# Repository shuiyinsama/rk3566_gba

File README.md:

# rk3566_gba

RK3566 / Radxa CM3 掌机验证项目。当前第一验证目标是 GBA，第一阶段使用 Radxa CM3 IO Board + 4.3 寸 HDMI 屏完成系统、显示、输入、音频、散热和 GBA 模拟器验证；成品阶段再围绕目标 DSI 屏设计自研 CM3 底板。

## 构建

项目使用 CMake 管理。

Windows 开发机建议通过 WSL Ubuntu 构建，不需要 SSH 到 WSL。SSH 主要用于后续连接 Radxa CM3 板端做实际硬件验证。

```bash
cmake --preset debug
cmake --build --preset debug
ctest --preset debug
./build/debug/rk3566-gba --help
```

若之前在 Windows 原生路径下生成过 `build/debug`，切到 WSL 后可能遇到 CMake cache 路径不匹配。删除 `build/debug` 后重新运行 `cmake --preset debug` 即可。

## 开发助手

Windows 上可以启动 Python 图形窗口，把 WSL 构建、同步源码、板端构建和板端验证做成按钮：

```powershell
python tools\radxa_dev_gui.py
```

首次连接板子时，先填写用户名和 IP，然后点“初始化 SSH 免密终端”，按提示输入一次板子密码。之后常用流程可以点“一键全流程”。

同步源码时优先使用板端 `rsync`。如果板端没有安装 `rsync`，开发助手会自动改用 `tar` 兜底同步；兜底同步可以继续推进验证，但不会删除板端已存在而本地已移除的旧文件。

进入 GBA 实测前，点“板端安装 GBA 工具”安装 `mgba-qt`、`retroarch` 和 `libretro-mgba`。这个步骤需要在弹出的终端里输入一次板子 sudo 密码。

第一阶段上板后先跑平台探测：

```bash
./build/debug/rk3566-gba probe
```

确认 HDMI、音频、输入和温度基线后，再进入 GBA 实测准备：

```bash
./build/debug/rk3566-gba gba-check
```

GBA 模拟器环境准备好后，可以用一键启动脚本切换 HDMI 分辨率并启动 mGBA：

```bash
bash ~/rk3566_gba/scripts/launch-gba.sh /home/radxa/roms/gba/pokemon-green.gba
```

开始 30 分钟稳定性记录时，可以直接在电脑上运行：

```powershell
python tools\monitor_gba_from_pc.py --launch --rom /home/radxa/roms/gba/pokemon-green.gba --duration 1800 --interval 10
```

这条命令会通过 WSL SSH 连接板子，先后台启动 mGBA，再把温度、CPU、内存、mGBA 进程和 HDMI 模式实时显示在电脑终端里；电脑端日志会写入 `logs/`，板端 CSV 和文本日志会写入 `~/rk3566_gba/logs/`。

如果模拟器已经在板子上运行，只想记录当前状态，可以去掉 `--launch`：

```powershell
python tools\monitor_gba_from_pc.py --duration 1800 --interval 10
```

如果 mGBA 无法直接识别 USB 手柄，但 `evtest` 能看到手柄事件，可以先用用户层映射脚本把手柄转换成 mGBA 默认键盘按键：

```bash
sudo python3 ~/rk3566_gba/scripts/gamepad-keyboard-bridge.py --event /dev/input/event3 --show-events
```

保持这个终端运行，再启动 mGBA。默认映射为方向键、`X`/`Z`、`Enter`、`Backspace`、`A`/`S`，对应 mGBA 常见默认键位。

音频验证可以先列出板端音频状态，再播放测试音：

```bash
bash ~/rk3566_gba/scripts/audio-check.sh
bash ~/rk3566_gba/scripts/audio-check.sh --play
```

如果默认设备没有声音，再根据 `aplay -l` 中的声卡编号尝试 `--device plughw:X,Y`。

退出和重启验证使用会话管理脚本：

```bash
bash ~/rk3566_gba/scripts/gba-session.sh status
bash ~/rk3566_gba/scripts/gba-session.sh stop
bash ~/rk3566_gba/scripts/gba-session.sh start /home/radxa/roms/gba/pokemon-green.gba
bash ~/rk3566_gba/scripts/gba-session.sh restart /home/radxa/roms/gba/pokemon-green.gba
```

一键掌机模式会把手柄映射和 mGBA 启动合在一起：

```bash
bash ~/rk3566_gba/scripts/gba-handheld.sh start /home/radxa/roms/gba/pokemon-green.gba
bash ~/rk3566_gba/scripts/gba-handheld.sh status
bash ~/rk3566_gba/scripts/gba-handheld.sh stop
```

手柄的 `/dev/input/eventX` 编号可能会变化，脚本会优先使用 `/dev/input/by-id/*event-joystick` 自动定位。需要排查时运行：

```bash
bash ~/rk3566_gba/scripts/gba-handheld.sh --list-gamepads
```

## 文档

- [RK3566 多模拟器掌机阶段方案](docs/hardware-selection.md)
- [阶段一 HDMI 验证清单](docs/phase1-hdmi-validation.md)
- [GBA 实测流程与记录](docs/gba-validation.md)
- [开发记录](docs/development-log.md)
- [Radxa CM3 IO Board DSI 接口分析](docs/cm3-io-dsi-analysis.md)
- [Waveshare 4inch DSI LCD 适配分析](docs/waveshare-4inch-dsi-lcd-analysis.md)
- [U90074 转 Waveshare 15-pin DSI 转接小板草案](hardware/u90074_to_waveshare_15pin_dsi/README.md)

## 当前路线

第一阶段使用 Radxa CM3 IO Board + 4.3 寸 HDMI 屏验证系统、模拟器性能、输入、音频、功耗和散热。DSI 屏和自研掌机底板放到第二阶段，在确认 RK3566 性能边界后再选型。

## 文档编码

本仓库 Markdown 文档使用 UTF-8。若在 PowerShell 或部分终端看到中文乱码，优先用 VS Code、Typora、Obsidian 或其它 UTF-8 Markdown 查看器打开。

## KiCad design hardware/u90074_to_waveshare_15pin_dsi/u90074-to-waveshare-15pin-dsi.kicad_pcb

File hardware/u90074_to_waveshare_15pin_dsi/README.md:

# U90074 to Waveshare 15-pin DSI Adapter

本目录是 RK3566 GBA 掌机项目的第一版 DSI 屏转接小板草案，用于把 Radxa CM3 IO Board 的 `U90074` 39-pin MIPI LCD 接口转到 Waveshare 4inch DSI LCD 的 Raspberry Pi 15-pin DSI 接口。

## 当前状态

- 状态：电气映射和布局草案，暂不建议直接投板。
- 输入接口：Radxa CM3 IO Board `U90074`，按原理图/netlist 中的 39-pin LCD 接口整理。
- 输出接口：Waveshare 4inch DSI LCD 的 15-pin Raspberry Pi DSI 接口。
- 屏幕只使用 2-lane DSI：`D0`、`D1`、`CLK`、`I2C`、`3V3`、`GND`。
- `U90074` 的 `D2/D3`、背光 LED、触摸复位/中断等信号本版不接出。

## 文件说明

- `pin-map.csv`：转接关系表，优先审查这个文件。
- `adapter-notes.md`：电气和 PCB 约束说明。
- `u90074-to-waveshare-15pin-dsi.kicad_pcb`：KiCad PCB 草案，含板框、占位 FPC 焊盘、网络名和测试点。
- `u90074-to-waveshare-15pin-dsi.kicad_pro`：KiCad 工程占位文件。
- `board-outline.svg`：布局和走线意图示意图。

## 需要二次确认

1. `U90074` 连接器的精确型号、pitch、接触面方向、翻盖方向和 pin 1 位置。
2. Waveshare 15-pin DSI FPC 的精确 pitch、接触面方向和 pin 1 位置。
3. `U90074` 是否存在额外 shield/mechanical GND pin。netlist 里出现过 40/41 接地信息，但原理图接口按 39-pin 使用。
4. `VCC_LCD_MIPI_2` 已在 CM3 IO Board 图纸中标注为 3.3V；投板前仍建议实测空载/带载电压。
5. Waveshare 屏触摸 I2C 默认使用 Pi 的 `I2C-0`，本适配板将其接到 CM3 IO Board 的 `I2C2_SCL_LCD/I2C2_SDA_LCD`，后续设备树需要匹配。

## 建议首版板子

- 2 层板即可做验证版，但 DSI 差分对需要尽量短、等长、连续参考地。
- 板宽按 40 mm 草案放置，后续按核心板、屏幕排线和外壳空间收缩。
- 保留 `3V3/GND/SCL/SDA` 测试点，方便点亮阶段排查。
- 不在本板做电平转换；如果后续确认触摸 I2C 电平不是 3.3V，再加器件。

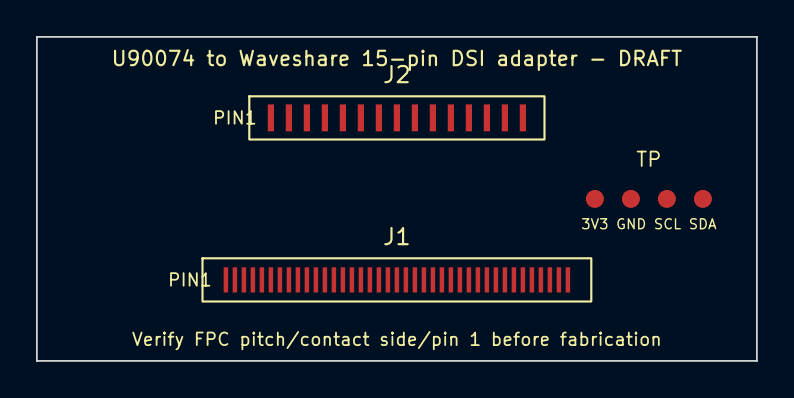
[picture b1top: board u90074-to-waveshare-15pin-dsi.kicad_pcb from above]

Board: 2 copper layers, 40.0 x 18.0 mm, 3 parts (0 on the bottom side), 12 nets, no tracks yet.

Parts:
J1: CM3_IO_U90074_39P; U90074_39P_PLACEHOLDER
J2: WAVESHARE_15P_DSI; WAVESHARE_15P_1MM_PLACEHOLDER
TP: VCC_GND_SCL_SDA; TESTPOINTS_1MM

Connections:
DSI_CLK_N: J1.13, J2.5
DSI_CLK_P: J1.14, J2.6
DSI_D0_N: J1.7, J2.8
DSI_D0_P: J1.8, J2.9
DSI_D1_N: J1.10, J2.2
DSI_D1_P: J1.11, J2.3
GND: J1.6, J1.9, J1.12, J1.15, J1.18, J1.21, J1.22, J1.28, J1.29, J1.32, J1.33, J2.1, J2.4, J2.7, J2.10, J2.13, TP.2
I2C_SCL_LCD: J1.27, J2.11, TP.3
I2C_SDA_LCD: J1.26, J2.12, TP.4
NC_LEDA: J1.38, J1.39
NC_LEDK: J1.34, J1.35
VCC_3V3_LCD: J1.1, J1.30, J1.31, J2.14, J2.15, TP.1

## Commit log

2026-06-16 增加选型文档
2026-06-16 增加CM3 IO Board原理图 增加Radxa CM3核心板pinout 增加4inch DSI LCD资料
2026-06-16 增加dsi屏转接小板
2026-06-16 更新硬件选型，屏幕改用hdmi屏
2026-06-16 搭建cmake结构
2026-06-17 更新阶段一测试记录模板，增加基本信息、系统启动、GBA测试及温度和功耗记录部分
2026-06-17 更新项目版本至0.2.0，增加阶段一验证工具命令行助手功能，支持生成测试记录和输出验证步骤
2026-06-17 26.6.17备份
2026-06-17 回退版本
2026-06-17 解决冲突
2026-06-17 新增平台探测功能，支持 HDMI、音频、输入和温度节点的基线检测
2026-06-21 更新开发日志
2026-06-21 新增 GBA 实测准备功能，包含检查模拟器和测试 ROM 路径的命令 `gba-check`，并更新相关文档。
2026-06-21 增加python开发窗口
2026-06-21 修复 WSL 启动时乱码提示，优化 SSH 免密初始化流程。
2026-06-21 python窗口新增“板端安装 GBA 工具”功能，支持在交互终端中安装 `mgba-qt`、`retroarch` 和 `libretro-mgba`。
2026-06-22 首次跑通mgba模拟器-记录日志
2026-06-24 增加一键启动脚本
2026-06-24 更新启动脚本为完整路径
2026-06-25 当前radxa内核没有joydev模块，增加xbox手柄映射
2026-06-27 新增音频验证脚本和重启脚本
2026-06-27 新增一键掌机模式脚本，合并手柄映射与mGBA启动流程
